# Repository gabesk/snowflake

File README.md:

# snowflake
 
# Welcome
Welcome to the 2021 Christmas card. This one’s a snowflake. Put a CR2032 battery in the back (flat side up, but don’t worry there’s a diode so putting it in backwards won’t hurt – it won’t do anything, but it won’t hurt either :P), and it should start twinkling. It’ll go on forever until the battery runs out, which I hope will take a few weeks at least.

# Design
There’s not enough pins to give every LED on the snowflake its own pin on the MCU, so they’re matrixed. The LED `+V` pins on each spire are controlled by a single pin on the MCU, so 6 bits total, `PC0-5`. Then, each LED in the same spot on each spire’s GND pin is controlled by a pin on the MCU, for a total of 8 bits, `PD0-7`. So, to turn on `LED0` on `spire 0`, you’d output high on `PC0` and output low on `PD0`. To turn the same LED on spire 1 on, it would be the same but you would output low on `PD1` instead.

Theoretically this means you can only have multiple different LEDs on the same spire illuminated if all the other spires are off, or the LED in the same spot will be lit on those spires as well. In practice, the firmware ignores those constraints and just picks two LEDs at random to twinkle, because it turns out the visual effect is interesting so whatever.

To get the snowflake shaped board, I looked around for snowflake SVG images, and found the one in the converter folder from FontAwesome.com. I then wrote a partial, hacky, SVG path parser and converted that to the corresponding Eagle board outline XML primitives. (Thankfully they’re the same primitives, so it just needed minor transformations. The biggest pain there was understanding the terrible SVG path format. You can really tell that specification was inherited from an old software project that was donated and came from an era with far more limited processing power. Also, as an aside, with that many curves in the board outline, Eagle’s default assisted routing is really, REALLY slow to route, which is why the routing looks like someone drew it with a crayon. Because I did. An unassisted software-crayon.)

The firmware itself is pretty simple. It software-PWMs the LEDs, and picks one or two to twinkle on and off at random. To save power, the MCU runs on the low-speed 128kHZ clock, which limits the software PWM to 2 LEDs. I’m sure you could do more at once with some optimization of the C code, but that’s already pretty optimized compared to the original version, and the matrixed LEDs means that more than 2 are frequently illuminated anyway, so I think it’s fine. But, it’s all open source, so ...

I don’t know how long the battery will last, but given the low-power clock is supposed to only take ~ 45 uA, probably at least as long as it takes you to throw out the Christmas tree, but probably not long enough to make it to next Christmas? Shrug.

# Other uses
Aside from being an interesting Christmas card ornament, it’s designed to be somewhat usable as a general-purpose Arduino-compatible AVR microcontroller. At every tip are standard 0.1 mm header holes, routed to various useful pins from the MCU.

## Programming
The default firmware doesn’t have a bootloader (which wouldn’t be very useful at the 128kHz clock speed anyway), but using something like the Sparkfun AVR Programmer, or just another Arduino, you can upload your own code. (Everything is 5 volt tolerant [by virtue of there being nothing on the board but LEDs :-D], so no worries about hooking it up directly to either.) Follow the hookup guide below, but be careful: there is no reverse-current protection between `V+` and `GND`:
 
One connected, the easiest way to program is to install Arduino and then run something like:

```Batchfile
"c:\Program Files (x86)\Arduino\hardware\tools\avr\bin\avrdude.exe" -C "C:\Program Files (x86)\Arduino\hardware\tools\avr\etc\avrdude.conf" -c usbtiny -p atmega328pb -U lfuse:w:0x62:m -B 250
```

to set the fuses back to the default 1 MHz clock (that’s the `0x62`), then

```Batchfile
"c:\Program Files (x86)\Arduino\hardware\tools\avr\bin\avrdude.exe" -C "C:\Program Files (x86)\Arduino\hardware\tools\avr\etc\avrdude.conf" -c usbtiny -p atmega328pb -U flash:w:sketch_dec20b.ino.hex
```

to upload your code (replacing the file with whatever your sketch is).

(As an aside, if you want to put the original snowflake firmware back on the board, the 128kHz clock fuse setting is `0xe3`.)

Note also that Arduino compiles into something like `C:\Users\Gabe\AppData\Local\Temp\arduino_build_696623`, so you can do

```
dir arduino_build* /od-
```

to find the directory of your most recently compiled sketch when you’re in the Temp directory, in order to get to the folder of your compiled sketch.

This all is written for Windows, but you can find the location on your platform by going to the Arduino preferences and clicking the *Show verbose output* options and observing the path.

## MiniCore
The snowflake has an **ATMega328PB** MCU, which is almost but not quite the same as the one in the Arduino Uno (lower power among other things). The **MiniCore** project supports this chip as well the internal oscillator (Uno has an external crystal). So, the easiest way to use the snowflake for something else is to install that project into Arduino, at which point you can do like it says and either continue using the programmer, or burn its bootloader to the chip and hook up a USB-serial converter to the appropriate pins. (Set the fuse back to 1MHz as above first.)

Which, speaking of:

## Exposed Pins
As much as possible I’ve routed out useful pins to the headers on the tips of the snowflake. These connections look a bit random but were chosen to expose the most useful pins 1st, and then for ease of routing 😊. Note that several pins have lines drawn from them to either LEDs or resistors (**LEDs**: `PD5, PD6, PD1`, **resistors:** `PC4, PC5`). These are shared with the matrixed LEDs. All LED pins are shared with every LED in that spot on each spire, and the resistors control all the LEDs on those two spires. Just keep that in mind when using these pins, as the current draw by the LEDs could cause unexpected signal issues.

Interesting exposed pin configurations:

* **UART0 Rx/Tx**: `PD0/PD1` (as well as 1k resistor limited Rx)
* `PB0-2`: This whole spire isn’t shared with any LEDs!
* **SPI0**: `MOSI, MISO, SCLK`, and `PB2 (~SS)` (and isn’t shared with LEDs either)
* **I2C0**: `PC4 (SDA), PC5 (SCL)`
* **I2C1**: `PE0 (SDA), PE1 (SCL)`, and isn’t shared with anything!
* `PD6`: Analog in 0

In other words, you’ve got a SPI and I2C bus both free from any LED interference, as well as a few more pins (`PB0 and PB1`).

And, if you don’t mind not using the LEDs, you can also use the hardware UART0, another I2C bus, and an analog input.

## Errata
Too late in the design process, I discovered I had used the wrong sized LED footprint, and the only ones in stock at JLCPCB assembly were white LEDs. Surprisingly, these light at the 3V of the CR2032 battery, but they are rather dim when placed inline with the 1k resistors. To solve that, you can either short out the resistors with a soldering iron, or you can hook up a 5 V power supply to the GND/5V pins on the snowflake. Sorry! 😊 (You could also stack two batteries on top of one another and hook that up, for ~6 V, which would be bright too, but won’t fit in the battery holder sadly.)

You’ve probably noticed from the bodge wire that there are a few issues with the design as is. The main one is that two of the spires’ LEDs aren’t connected, because of routing errors in the PCB.

The other is that I put a 1K resistor on the UART Rx (into MCU) line, so that you can safely feed signals from a 5V USB-serial converter even if the board is powered at 3.3V (by virtue of the input protection diodes). However, I didn’t think about the fact that the more common scenario is that it’s powered by a USB-serial adapter which supplies raw USB power (~5V) but inputs and outputs 3.3V. In that case, the Tx line is the one that needs protection and there isn’t any. So, you’d have to add your own. That’s probablSy not a big hassle given you’ll already have to add a pull-up resistor and capacitor or a RST button/wire if you’re going to use serial programming anyway, but just something to be aware of.

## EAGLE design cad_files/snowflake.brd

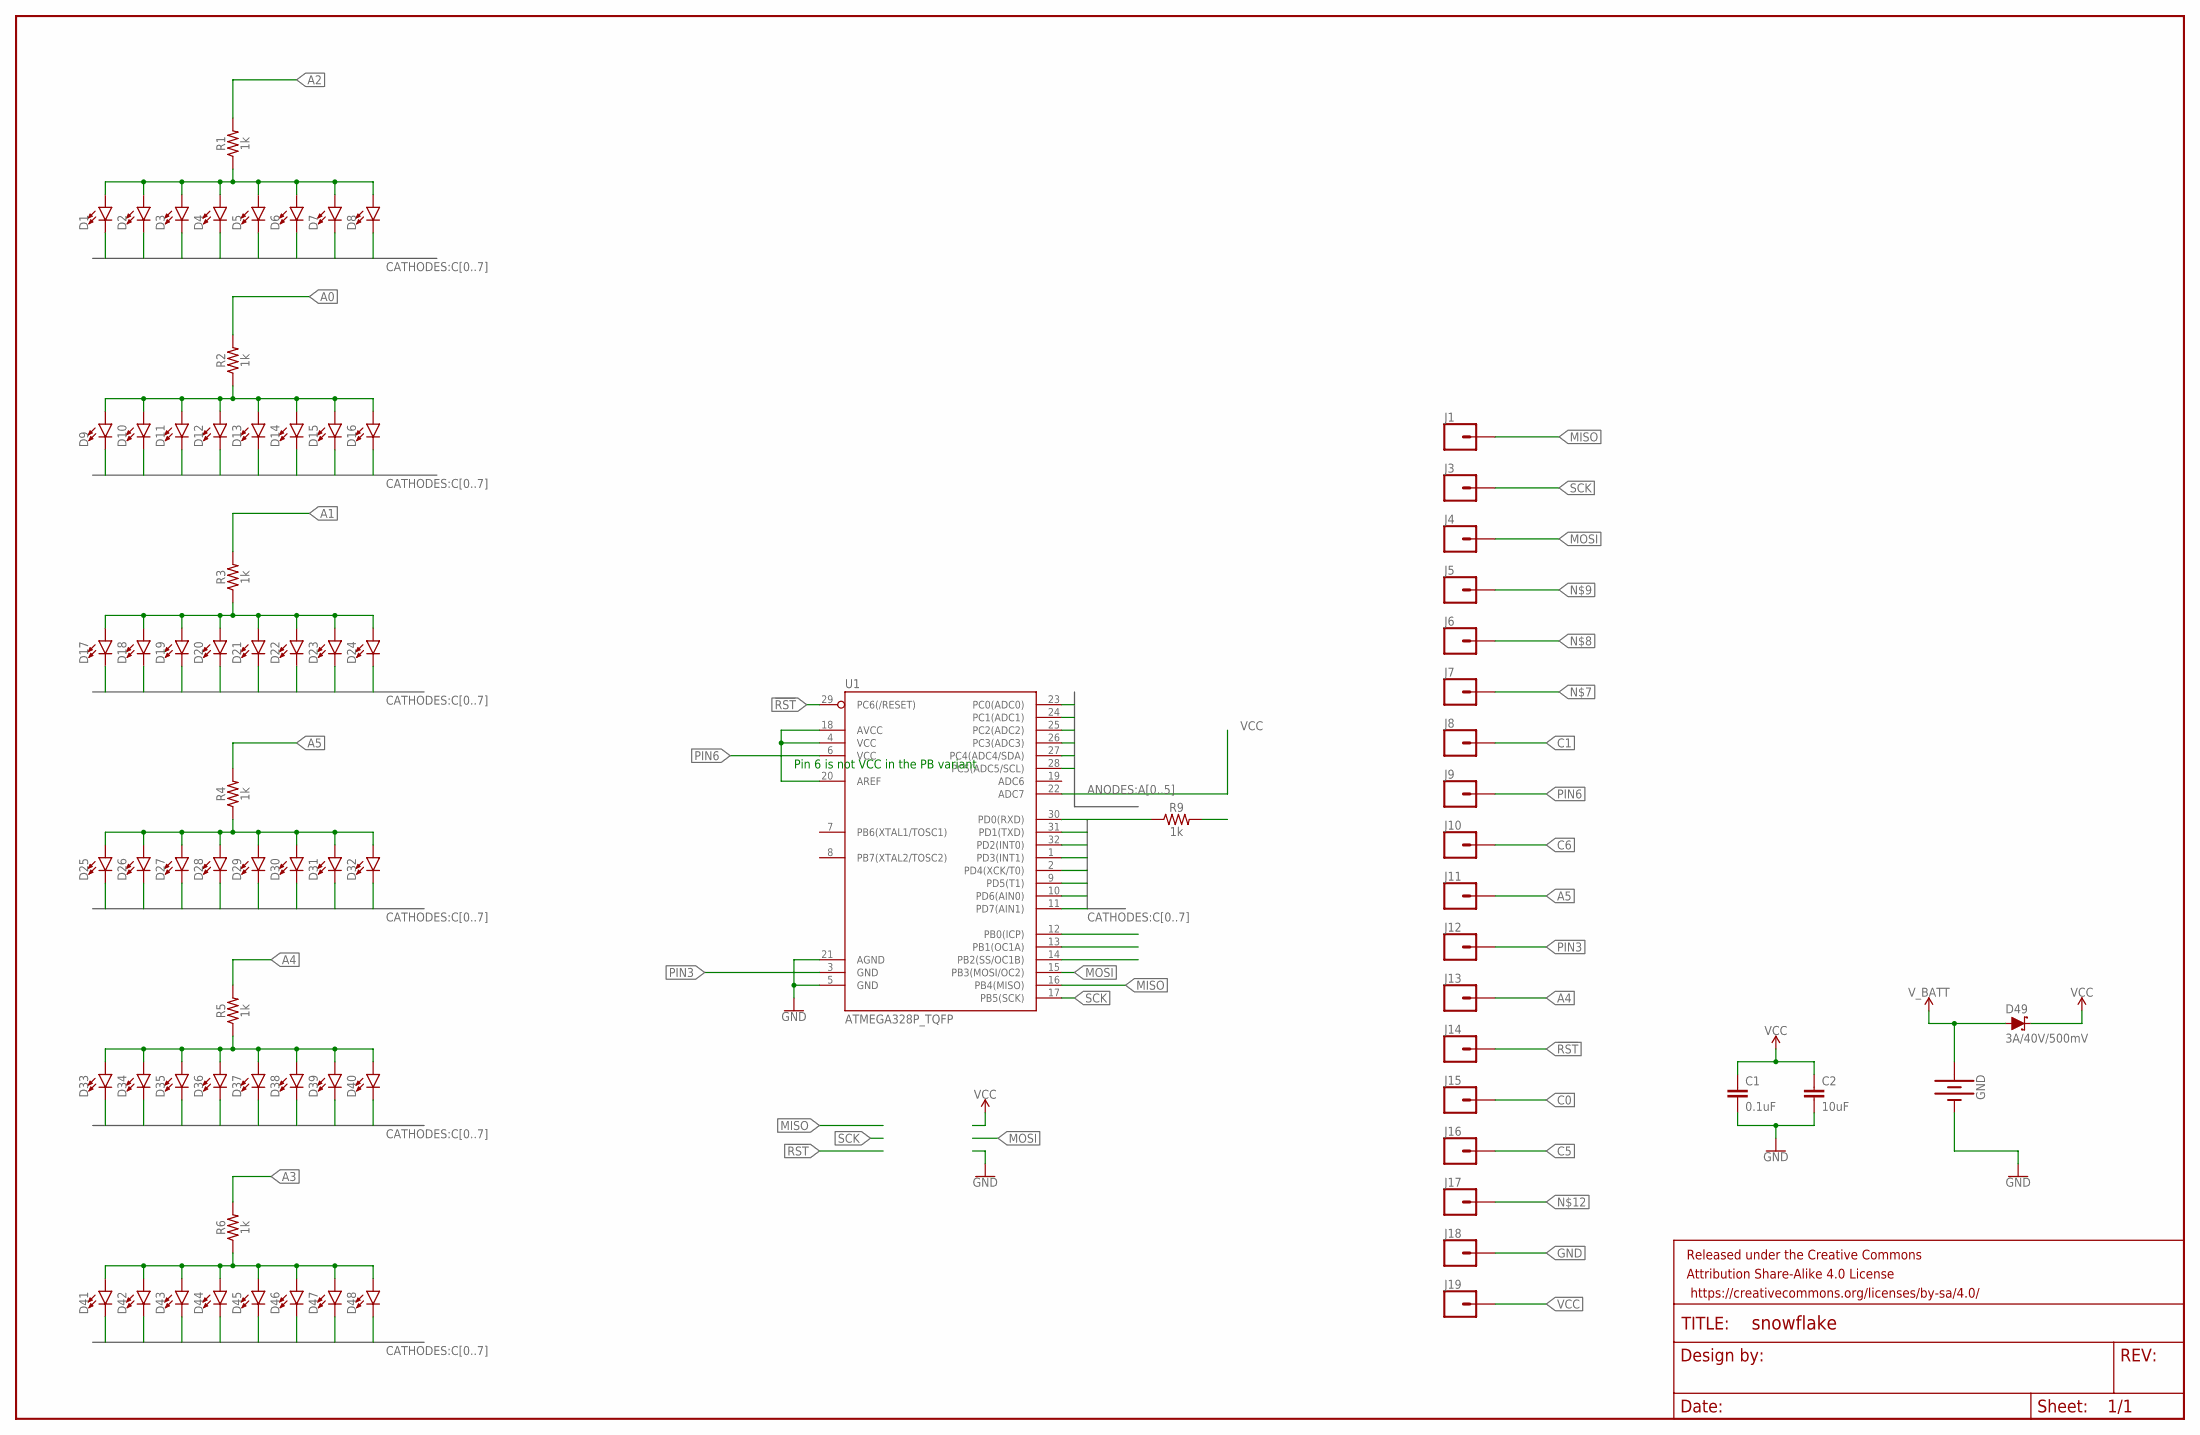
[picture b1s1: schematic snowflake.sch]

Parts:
C1: 0.1uF; 0603
C2: 10uF; 0805
D1, D2, D3, D4, D5, D6, D7, D8, D9, D10, D11, D12, D13, D14, D15, D16, D17, D18, D19, D20, D21, D22, D23, D24, D25, D26, D27, D28, D29, D30, D31, D32, D33, D34, D35, D36, D37, D38, D39, D40, D41, D42, D43, D44, D45, D46, D47, D48: LED1206; LED-1206
D49: 3A/40V/500mV; SMA-DIODE
FRAME1: FRAME-LEDGER; CREATIVE_COMMONS
GND: BATTERY-20MM_SMD; BATTCON_20MM
J1, J3, J4, J5, J6, J7, J8, J9, J10, J11, J12, J13, J14, J15, J16, J17, J18, J19: CONN_01; 1X01
R1, R2, R3, R4, R5, R6, R9: 1k; 0603
U1: ATMEGA328P_TQFP; TQFP32-08

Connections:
!RST: J14.1, U1.29 (PC6(/RESET))
A0: R2.2, U1.23 (PC0(ADC0))
A1: R3.2, U1.24 (PC1(ADC1))
A2: R1.2, U1.25 (PC2(ADC2))
A3: R6.2, U1.26 (PC3(ADC3))
A4: J13.1, R5.2, U1.27 (PC4(ADC4/SDA))
A5: J11.1, R4.2, U1.28 (PC5(ADC5/SCL))
C0: D1.C, D9.C, D17.C, D25.C, D33.C, D41.C, J15.1, R9.1, U1.30 (PD0(RXD))
C1: D2.C, D10.C, D18.C, D26.C, D34.C, D42.C, J8.1, U1.31 (PD1(TXD))
C2: D3.C, D11.C, D19.C, D27.C, D35.C, D43.C, U1.32 (PD2(INT0))
C3: D4.C, D12.C, D20.C, D28.C, D36.C, D44.C, U1.1 (PD3(INT1))
C4: D5.C, D13.C, D21.C, D29.C, D37.C, D45.C, U1.2 (PD4(XCK/T0))
C5: D6.C, D14.C, D22.C, D30.C, D38.C, D46.C, J16.1, U1.9 (PD5(T1))
C6: D7.C, D15.C, D23.C, D31.C, D39.C, D47.C, J10.1, U1.10 (PD6(AIN0))
C7: D8.C, D16.C, D24.C, D32.C, D40.C, D48.C, U1.11 (PD7(AIN1))
GND: C1.2, C2.2, GND.2 (-), J18.1, U1.5 (GND), U1.21 (AGND)
MISO: J1.1, U1.16 (PB4(MISO))
MOSI: J4.1, U1.15 (PB3(MOSI/OC2))
unnamed: D1.A, D2.A, D3.A, D4.A, D5.A, D6.A, D7.A, D8.A, R1.1
unnamed: D9.A, D10.A, D11.A, D12.A, D13.A, D14.A, D15.A, D16.A, R2.1
unnamed: D17.A, D18.A, D19.A, D20.A, D21.A, D22.A, D23.A, D24.A, R3.1
unnamed: D25.A, D26.A, D27.A, D28.A, D29.A, D30.A, D31.A, D32.A, R4.1
unnamed: D33.A, D34.A, D35.A, D36.A, D37.A, D38.A, D39.A, D40.A, R5.1
unnamed: D41.A, D42.A, D43.A, D44.A, D45.A, D46.A, D47.A, D48.A, R6.1
unnamed: J7.1, U1.12 (PB0(ICP))
unnamed: J6.1, U1.13 (PB1(OC1A))
unnamed: J5.1, U1.14 (PB2(SS/OC1B))
unnamed: J17.1, R9.2
PIN3: J12.1, U1.3 (GND)
PIN6: J9.1, U1.6 (VCC)
SCK: J3.1, U1.17 (PB5(SCK))
VCC: C1.1, C2.1, D49.C, J19.1, U1.4 (VCC), U1.18 (AVCC), U1.20 (AREF), U1.22 (ADC7)
V_BATT: D49.A, GND.1 (+)

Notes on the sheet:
Pin 6 is not VCC in the PB variant

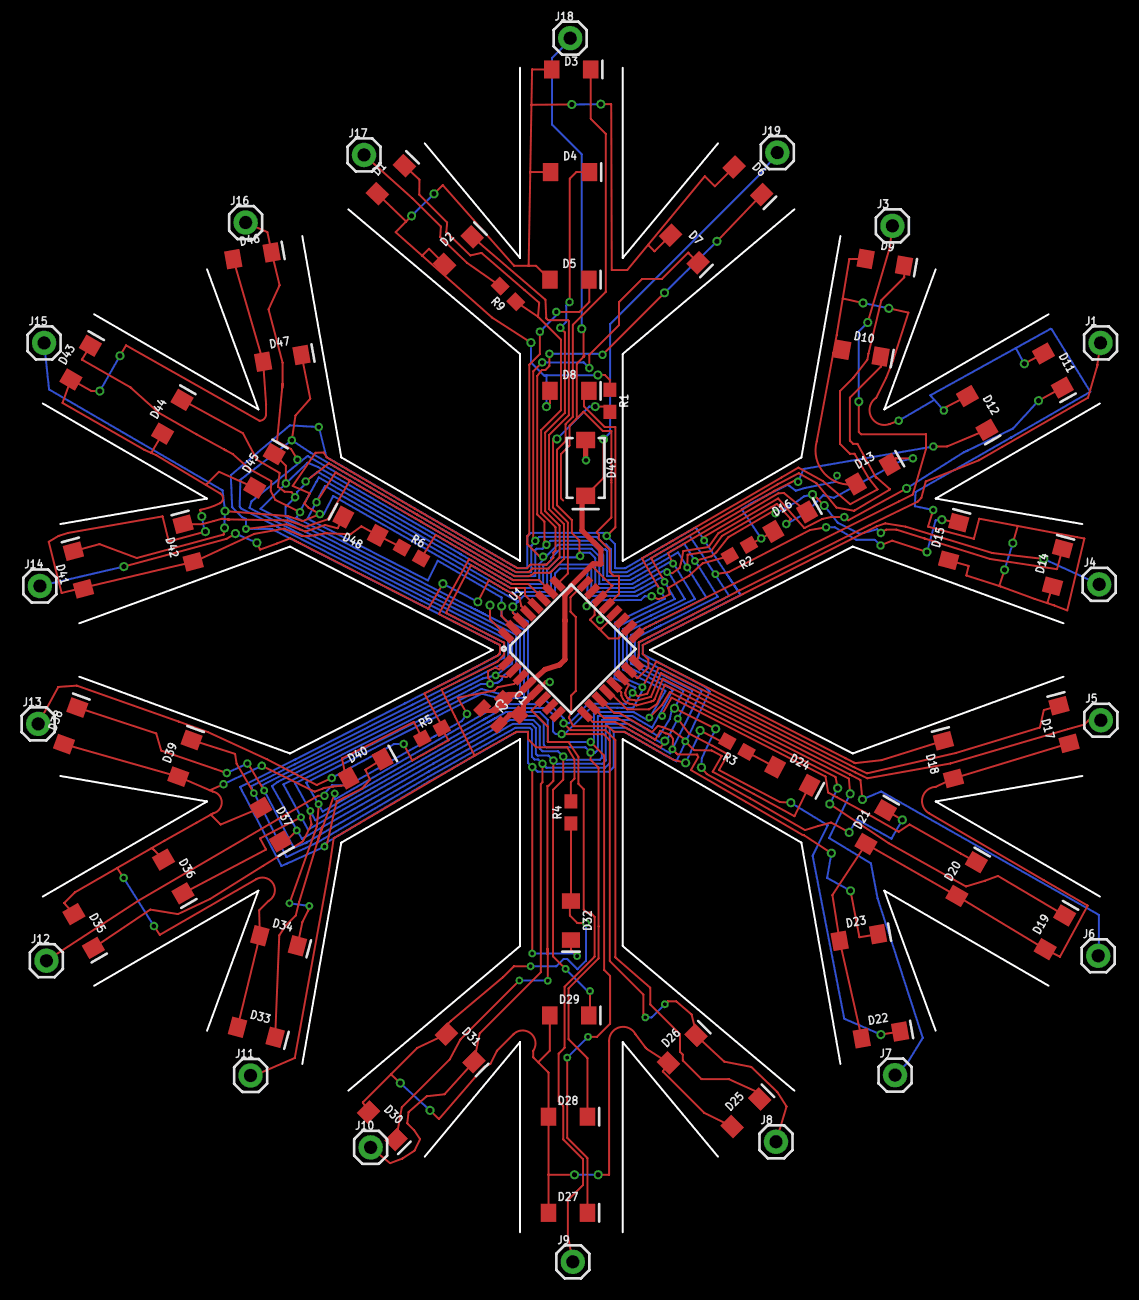
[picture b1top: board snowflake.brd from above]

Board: 2 copper layers, 81.4 x 89.7 mm, 79 parts (1 on the bottom side), 33 nets.

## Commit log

2021-12-24 Add snowflake source file
2021-12-24 Update attribution of snowflake outline

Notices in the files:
parts and their libraries:
SparkFun-LED: Licensing: Creative Commons ShareAlike 4.0 International - https://creativecommons.org/licenses/by-sa/4.0
SparkFun-Aesthetics: Released under the Creative Commons Attribution Share-Alike 4.0 License
SparkFun-Aesthetics: https://creativecommons.org/licenses/by-sa/4.0
